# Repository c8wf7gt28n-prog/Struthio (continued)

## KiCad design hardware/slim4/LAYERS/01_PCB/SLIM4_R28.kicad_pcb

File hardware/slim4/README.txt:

STRUTHIO SLIM4 — R32 PACKAGE

R32 puts PCB R27 in the package: PCB R26 with the margins found by a five-part pre-order review
(CHECKS/PREORDER_REVIEW_R26/: power, processor, display, audio and controls, firmware; no blocker in
the hardware). 31 ground vias in U1's exposed pad (R26: 4), each on the pad's copper; 10 uF at
U1's core supply pins; a second 1 uF on the backlight output and a 60 V backlight diode; R424
beside the charger (BQ_TS 5.2 mm, was 88 mm); 22 ohm on the USB data lines; silkscreen labels at
the battery, speaker and button positions. The ground under the core regulator's feedback and
enable routes is checked unbroken (LAYERS/01_PCB/R27_FROM_R26/PLANE_CHECK_R27.txt). The DSI pairs,
pins, ports and outline are unchanged. Four parts plug into it with no soldering and no adapter
cables: the Crystalfontz 5 in panel (its own tail into J1), a protected 1-cell battery of 1000 mAh
or more (JST PH, reverse-polarity switch), and two speakers (Molex PicoBlade). The firmware for it
is firmware/slim4 in the repository (R12: a hardware self-test at every boot and a USB console for
bring-up, docs/FIRST_BOOT.md). LAYERS/01_PCB/BRINGUP_PROCEDURE.md is the probe procedure for the
first boards. What R32 decided and why is in DECISIONS_R32.md (R31's to R26's decisions still hold
where not replaced). The case was set aside by the owner.

  01_PCB          R27: the four plug-in ports, a top-contact display socket on the front under the
                  panel, DSI coupled pairs from U1 to J1 over ground with return vias, power planes and
                  datasheet layouts for the 3.3 V, 1.2 V and backlight converters, 31 ground vias in
                  U1's exposed pad, 74 mA backlight, 0.5 A charging. JLCPCB order
                  files are generated by CHECKS/build_builder_packs.py. KiCad DRC 0/0/0.
                  One part to source: U1 (ESP32-P4NRW32X) had no stock on 2026-10-07.
  02_CASE         R12: complete enclosure, converged on R21 for a HOTHMI-size panel. Set aside:
                  its pass for the 5 in panel and the R23-R27 connectors is open.
  03_ACRYLIC      R2: clear unprinted face film (on hold with the case).

CHECKS/convergence_check.py tests every interface between the layers:
  - board against the walls, LCD against the shell, caps against the switches, film against the relief;
  - parts against parts, at rest and pressed;
  - supports against pads, joints, speakers, USB-C and battery;
  - J1's 40 pads against the panel's published pin table (N1).
Result: 78 PASS · 3 FAIL · 9 GATE · 3 INFO (CHECKS/R32_CONVERGENCE_REPORT.md).
The 3 FAIL rows are the set-aside case: the 5 in panel does not fit the R12 pocket (C6), and the
rear shell meets the new J3/J5 bodies and sits 0.08 mm from J4 (F1, G1). PRODUCTION_GATES.md lists
what is open, in the order to do it.

Shared CAD datum: millimetres, SLIM4 PCB XY (R21 = R22 = R23 = R24 = R25 = R26 = R27; Y down), board bottom at Z=0, +Z
toward the front.

Start with:
  index.html                          the studio: PCB, CASE and ACRYLIC layers; copper pours,
                                      BOM and sourcing for each part, fab status, open items; a guided tour;
                                      SYSTEMS (the board by function), BENCH (a bring-up record per board,
                                      step by step, exported as JSON/CSV) and DOCS (these documents, offline)
  PRODUCTION_GATES.md                 what to order now, then, and in the case pass
  LAYERS/01_PCB/README_PCB_LAYER.md   R27, R26, R25, R24 and R23 changes, battery, sourcing U1, rebuild
  LAYERS/01_PCB/BRINGUP_PROCEDURE.md  probing the first boards, phase by phase
  CHECKS/PREORDER_REVIEW_R26/         the five pre-order reviews
  CHECKS/R27_DSI_REPORT.md            the DSI pairs measured on the board
  LAYERS/01_PCB/DISPLAY_PORT.md       the panel, the J1 pinout and how the tail folds in
  LAYERS/01_PCB/FIRMWARE_PINMAP.md    every ESP32-P4 GPIO, for the firmware
  LAYERS/01_PCB/RELEASE_GATES.md      what is closed and open on the board
  CHECKS/R32_CONVERGENCE_REPORT.md    what was checked
  AI_CHANGE_REPORT_R32.md, CHANGELOG.md

Package layout:
  LAYERS/01_PCB          R27 KiCad board, project, footprints, layer JSON, DRC, reviews,
                         bring-up procedure, R27_FROM_R26/, R26_FROM_R25/, R25_FROM_R24/, R24_FROM_R23/, R23_FROM_R22/ and R22_FROM_R21/ (the scripted edits)
  LAYERS/02_CASE         CASE R12 source (build_r12.py, export_layer_formats.py) and exports;
                         the same source also builds the ACRYLIC film
  LAYERS/03_ACRYLIC      film R2 outputs
  ASSEMBLY/              PCB, case and film in one STEP, and the build order
  CHECKS/                convergence checker and reports, PCB layer exporter, renderer and renders,
                         component heights, BOM sourcing, fab summary, DSI pair check, pre-order reviews, manifest,
                         viewer-bundle and builder-file generators
  REFERENCES/            reference only: PCB R26, R25, R24, R23, R22 and R21, the R22 display flex, the R10 fit study,
                         the SLIM4 R3 study, the CASE R13 symmetric-controls prototype and the R1 outline study
  root                   studio (index.html, app.js, eye.js, styles.css, eye.css, model-data.js,
                         case-layer-data.js, acrylic-layer-data.js, case-r3-data.js, case-r13-data.js,
                         bench.js, bench.css, bench-data.js,
                         R27_REAR_BOARD.svg, sw.js, manifest, icons), package docs,
                         requirements.txt, PROJECT_MANIFEST.json, SHA256SUMS.txt

Regenerate everything (Python 3.13 with requirements.txt; KiCad 7.0.x for the PCB steps, with its
pcbnew module importable from that Python). Run from
the package root, in this order:
  python3 CHECKS/export_pcb_layer.py LAYERS/01_PCB/SLIM4_R27.kicad_pcb REFERENCES/PCB_R21/SLIM4_R21_PCB_LAYER.json \
      LAYERS/01_PCB/SLIM4_R27_PCB_LAYER.json R27 "STRUTHIO SLIM4 PCB R27" "Order files ready · U1 stock to confirm"
                                         (only after a PCB edit; then update the A1 hashes)
  python3 CHECKS/dsi_pair_check.py LAYERS/01_PCB/SLIM4_R27.kicad_pcb CHECKS/R27_DSI_REPORT   (after a PCB edit)
  python -B LAYERS/02_CASE/export_layer_formats.py
  python -B CHECKS/build_builder_packs.py <folder outside the package>
                                         (writes CHECKS/R27_FAB_SUMMARY.json)
  python -B CHECKS/convergence_check.py
  python -B CHECKS/build_builder_packs.py <folder outside the package>   (again: its README quotes the report)
  python -B CHECKS/render_review.py
  python -B CHECKS/build_pcb_viewer_data.py      (also the SYSTEMS map: every part and net assigned, or it stops)
  python -B CHECKS/build_bench_data.py           (bring-up steps and documents for BENCH and DOCS)
  python -B CHECKS/build_r13_reference_data.py   (the R13 controls prototype layer)
  python -B CHECKS/make_manifest.py      (last)

Files for the builders:
  python -B CHECKS/build_builder_packs.py <folder outside the package>
writes STRUTHIO_SLIM4_R32_BUILDER_FILES/ and its zip:
  1_PCB_FABRICATION  JLCPCB order: Gerbers, drill, BOM, CPL, README with every option and the
                     four plug-in parts
  2_3D_PRINTING      case R12 parts. On hold: do not print before the case pass.
  3_ACRYLIC_STICKER  face film, tapes, cover glass (on hold with the case)
The board is plotted from a temporary copy, with its hash checked before and after.

Deploying the studio: publish a bundle, not this folder.
  python -B CHECKS/build_viewer_bundle.py <folder outside the package>
writes 7 files: index.html, studio.js, R27_REAR_BOARD.svg, sw.js, manifest and two icons.

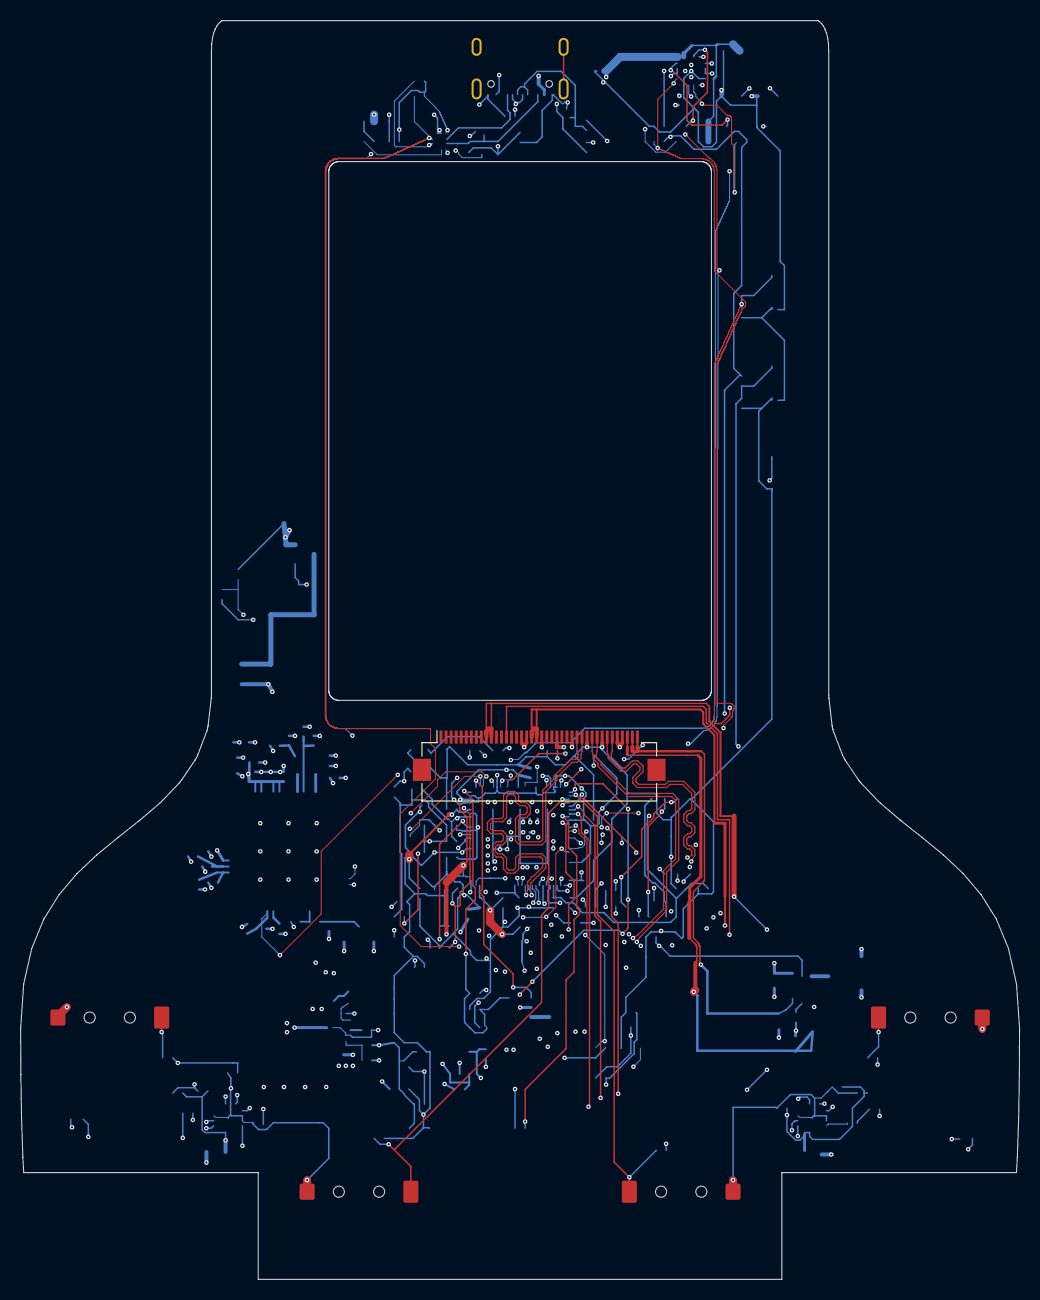
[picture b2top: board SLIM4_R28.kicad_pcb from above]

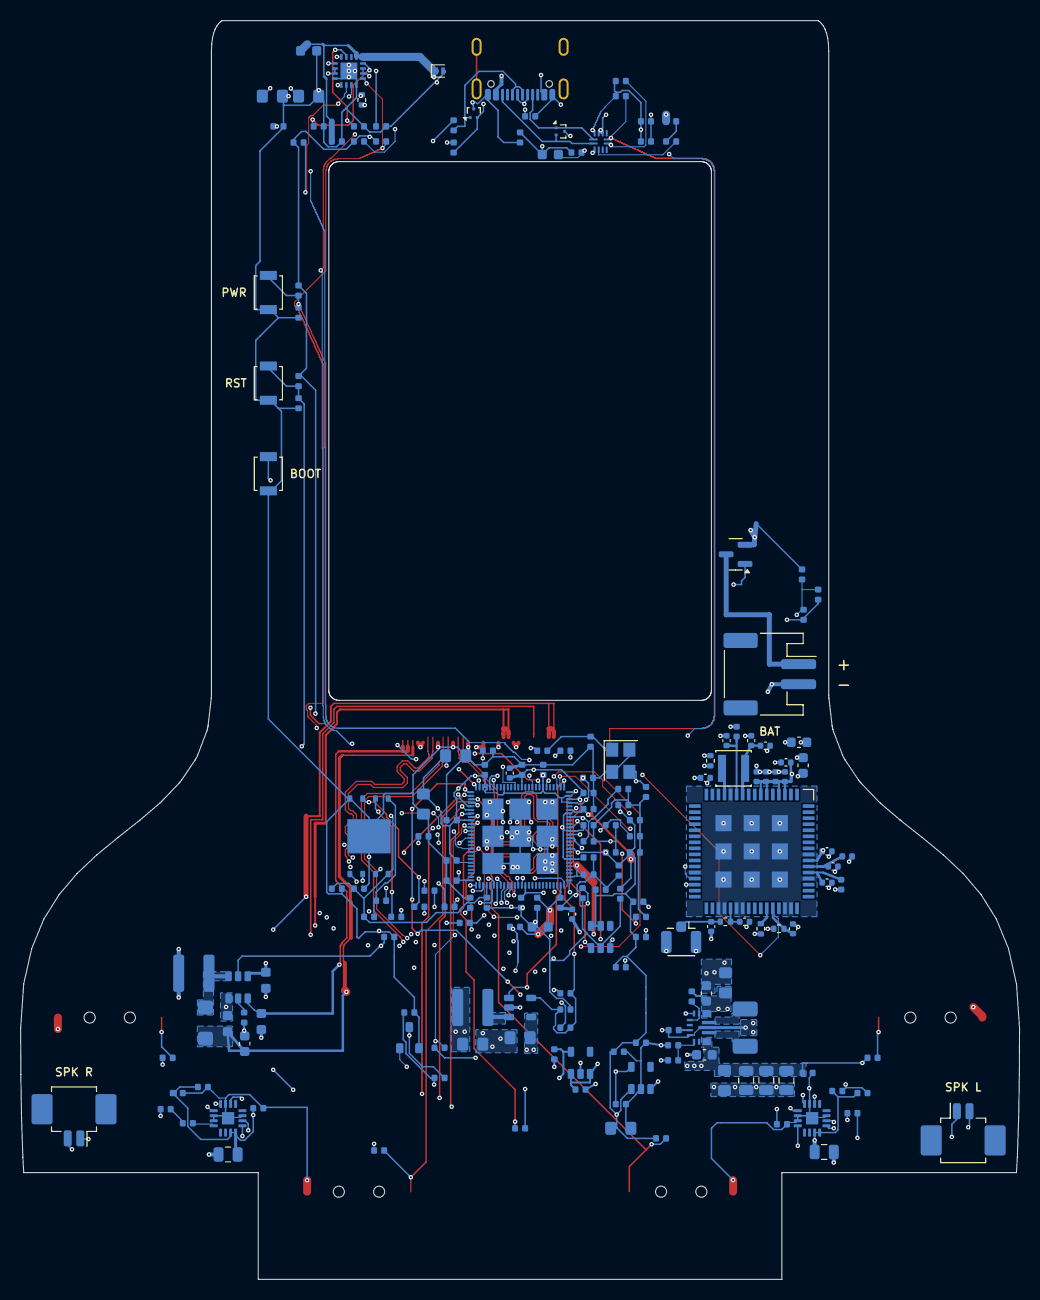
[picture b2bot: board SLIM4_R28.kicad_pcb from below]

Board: 6 copper layers, 99.2 x 125.0 mm, 194 parts (189 on the bottom side), 104 nets.

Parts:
C101: CL05B104KO5NNNC; FP_C101
C102: CL05B104KO5NNNC; FP_C102
C103: CL05B104KO5NNNC; FP_C103
C104: CL05B104KO5NNNC; FP_C104
C105: CL05B104KO5NNNC; FP_C105
C106: CL05B104KO5NNNC; FP_C106
C107: CL05B103KB5NNNC; FP_C107
C108: CL05B104KO5NNNC; FP_C108
C109: CL05A105KA5NQNC; FP_C109
C110: CL05B103KB5NNNC; FP_C110
C111: CL05B104KO5NNNC; FP_C111
C112: CL10A475KO8NNNC; FP_C112
C113: CL05B104KO5NNNC; FP_C113
C114: CL05B104KO5NNNC; FP_C114
C115: CL05A105KA5NQNC; FP_C115
C116: CL05B104KO5NNNC; FP_C116
C117: CL05B104KO5NNNC; FP_C117
C118: CL05A105KA5NQNC; FP_C118
C119: CL05A105KA5NQNC; FP_C119
C120: CL05A105KA5NQNC; FP_C120
C121: CL05A105KA5NQNC; FP_C121
C122: CL05A105KA5NQNC; FP_C122
C123: CL21A106KAYNNNE; FP_C123
C124: CL05B104KO5NNNC; FP_C124
C125: CL05B104KO5NNNC; FP_C125
C126: CL21A106KAYNNNE; FP_C126
C127: CL05B104KO5NNNC; FP_C127
C128: CL05B104KO5NNNC; FP_C128
C129: CL05B104KO5NNNC; FP_C129
C130: CL05B104KO5NNNC; FP_C130
C131: CL05B104KO5NNNC; FP_C131
C132: CL05B104KO5NNNC; FP_C132
C133: CL21A106KAYNNNE; FP_C133
C134: 0402 C0G 22pF; FP_C134
C135: CL21A226MQQNNNE; FP_C135
C136: CL05A105KA5NQNC; FP_C136
C138: CL05A106MQ5NUNC; FP_C138
C139: CL05A106MQ5NUNC; FP_C139
C140: CL10A105KB8NNNC; FP_C140
C201: CL05B104KO5NNNC; FP_C201
C202: CL05A105KA5NQNC; FP_C202
C203: 0402CG120J500NT; FP_C203
C204: 0402CG120J500NT; FP_C204
C302: CL05B104KO5NNNC; FP_C302
C303: CL05B104KO5NNNC; FP_C303
C304: CL05B104KO5NNNC; FP_C304
C305: CL05A105KA5NQNC; FP_C305
C306: CL05A105KA5NQNC; FP_C306
C307: CL05A105KA5NQNC; FP_C307
C308: CL05A105KA5NQNC; FP_C308
C309: CL10A105KB8NNNC; FP_C309
C310: CL05B224KO5NNNC; FP_C310
C311: CL10A475KO8NNNC; FP_C311
C401: CL05B104KO5NNNC; FP_C401
C402: CL10A106KP8NNNC; FP_C402
C403: CL05B104KO5NNNC; FP_C403
C404: CL05B104KO5NNNC; FP_C404
C406: CL05B104KO5NNNC; FP_C406
C407: CL05B104KO5NNNC; FP_C407
C408: CL05A105KA5NQNC; FP_C408
C409: CL10A475KO8NNNC; FP_C409
C410: CL10A475KO8NNNC; FP_C410
C411: CL21A106KAYNNNE; FP_C411
C412: CL21A106KAYNNNE; FP_C412
C413: CL21A226MQQNNNE; FP_C413
C414: CL21A226MQQNNNE; FP_C414
C415: CL21A226MQQNNNE; FP_C415
C416: CL10A106KP8NNNC; FP_C416
C417: CL21A226MQQNNNE; FP_C417
C418: CL21A226MQQNNNE; FP_C418
C419: CL21A226MQQNNNE; FP_C419
C420: CL21A106KAYNNNE; FP_C420
C421: CL21A106KAYNNNE; FP_C421
C501: CL05B104KO5NNNC; FP_C501
C502: CL05B104KO5NNNC; FP_C502
C503: CL05B104KO5NNNC; FP_C503
C504: CL05B104KO5NNNC; FP_C504
C505: CL05A105KA5NQNC; FP_C505
C506: CL05A105KA5NQNC; FP_C506
C601: CL05B104KO5NNNC; FP_C601
C602: CL05B104KO5NNNC; FP_C602
C603: CL05B104KO5NNNC; FP_C603
C701: CL05A106MQ5NUNC; FP_C701
C711: CL05B104KO5NNNC; FP_C711
C712: CL05A105KA5NQNC; FP_C712
C713: CL05B104KO5NNNC; FP_C713
C714: CL05B104KO5NNNC; FP_C714
C715: CL05A105KA5NQNC; FP_C715
C716: CL10A475KO8NNNC; FP_C716
C717: CL10A475KO8NNNC; FP_C717
C718: CL05A474KA5NNNC; FP_C718
C719: CL05B104KO5NNNC; FP_C719
C720: CL05B104KO5NNNC; FP_C720
C721: CL05B104KO5NNNC; FP_C721
C722: CL05A105KA5NQNC; FP_C722
C723: CL05A105KA5NQNC; FP_C723
C724: DNP; FP_C724
C725: DNP; FP_C725
C726: CL05B104KO5NNNC; FP_C726
D1: PESD5V0S1UL,315; FP_D1
D2: STPS1L60ZFY; FP_D2
E701: BLM15AG121SN1D; FP_E701
E702: BLM15AG121SN1D; FP_E702
E703: BLM15AG121SN1D; FP_E703
J1: FH12A-40S-0.5SH(55); FP_J1
J2: USB4105-GF-A-120; FP_J2
J3: S2B-PH-SM4-TB(LF)(SN); FP_J3
J4: 53261-0271; FP_J4
J5: 53261-0271; FP_J5
J701: U.FL-R-SMT-1(10); FP_J701
L1: MWSA0402S-1R0MT; FP_L1
L2: ASWPA4035S2R2MT; FP_L2
L3: WPN4020H100MT; FP_L3
L701: SWPA3012S150MT; FP_L701
Q1: 2N7002; FP_Q1
Q2: AO3401A; FP_Q2
R103: 0402WGF4021TCE; FP_R103
R104: 0402WGF4993TCE; FP_R104
R105: 0402WGF4993TCE; FP_R105
R106: 0402WGF1002TCE; FP_R106
R107: 0402WGF1002TCE; FP_R107
R108: 0402WGF1002TCE; FP_R108
R109: 0402WGF1002TCE; FP_R109
R110: 0402WGF1002TCE; FP_R110
R111: 0402WGF1002TCE; FP_R111
R112: 0402WGF1002TCE; FP_R112
R201: 0402WGF0000TCE; FP_R201
R202: 0402WGF0000TCE; FP_R202
R203: 0402WGF0000TCE; FP_R203
R204: 0402WGF0000TCE; FP_R204
R205: 0402WGF0000TCE; FP_R205
R206: 0402WGF0000TCE; FP_R206
R207: 0402WGF0000TCE; FP_R207
R208: 0402WGF0000TCE; FP_R208
R209: 0402WGF1002TCE; FP_R209
R307: 0402WGF1002TCE; FP_R307
R308: 0402WGF1003TCE; FP_R308
R309: 0603WAF270KT5E; FP_R309
R401: 0402WGF220JTCE; FP_R401
R402: 0402WGF220JTCE; FP_R402
R403: 0402WGF0000TCE; FP_R403
R404: 0402WGF0000TCE; FP_R404
R410: 0402WGF4703TCE; FP_R410
R411: 0402WGF1503TCE; FP_R411
R412: 0402WGF1801TCE; FP_R412
R413: 0402WGF3301TCE; FP_R413
R415: 0402WGF1501TCE; FP_R415
R416: 0402WGF4703TCE; FP_R416
R417: 0402WGF4303TCE; FP_R417
R418: 0402WGF1003TCE; FP_R418
R419: 0402WGF3302TCE; FP_R419
R420: 0402WGF1003TCE; FP_R420
R421: 0402WGF1003TCE; FP_R421
R422: 0402WGF1003TCE; FP_R422
R423: 0402WGF1003TCE; FP_R423
R424: 0402WGF1002TCE; FP_R424
R501: 0402WGF2001TCE; FP_R501
R502: 0402WGF1003TCE; FP_R502
R503: 0402WGF1103TCE; FP_R503
R504: 0402WGF1003TCE; FP_R504
R601: 0402WGF1002TCE; FP_R601
R602: 0402WGF1002TCE; FP_R602
R603: 0402WGF1002TCE; FP_R603
R604: 0402WGF1002TCE; FP_R604
R605: 0402WGF1002TCE; FP_R605
R606: 0402WGF1002TCE; FP_R606
R607: 0402WGF1002TCE; FP_R607
R701: 0402WGF0000TCE; FP_R701
R702: 0402WGF1002TCE; FP_R702
R703: 0402WGF1002TCE; FP_R703
R704: 0402WGF0000TCE; FP_R704
SW1: D2LS-21; FP_SW1
SW2: D2LS-21; FP_SW2
SW3: D2LS-21; FP_SW3
SW4: D2LS-21; FP_SW4
SW5: B3U-1000P; FP_SW5
SW6: B3U-1000P; FP_SW6
SW7: B3U-1000P; FP_SW7
U1: ESP32-P4NRW32X; FP_U1
U2: W25Q512JVEIQ TR; FP_U2
U3: TLV62569DBVR; FP_U3
U4: TPS63070RNMR; FP_U4
U5: TLV75518PDBVR; FP_U5
U6: ME6211C30M5G-N; FP_U6
U7: TPS61165DBVR; FP_U7
U8: MAX98357AETE+T; FP_U8
U9: MAX98357AETE+T; FP_U9
U10: BQ24074RGTR; FP_U10
U11: TPD2EUSB30DRTR; FP_U11
U12: TPD2EUSB30DRTR; FP_U12
U13: TUSB320LAIRWBR; FP_U13
U14: TPS3808G33DBVR; FP_U14
U15: RAK3172-SIP-9-SM-NI; FP_U15
Y1: L327S400H11L; FP_Y1

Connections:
1V1_HP: C103.1, C105.1, C125.1, C129.1, C134.1, C135.1, C138.1, C139.1, L2.2, R104.1, U1.26, U1.54, U1.76, U1.91
3V3_ENABLE: R423.2, U4.1, U4.14
3V3_SYS: C101.1, C102.1, C106.1, C114.1, C117.1, C123.1, C124.1, C126.1, C127.1, C128.1, C130.1, C131.1, C132.1, C133.1, C302.1, C303.1, C305.1, C307.1, C404.1, C406.1, C407.1, C408.1, C410.1, C414.1, C415.1, C416.1, C417.1, C418.1, C419.1, R106.1, R108.1, R109.1, R110.1, R111.1, R112.1, R308.1, R403.1, R410.1, R420.1, R421.1, R601.1, R602.1, R603.1, R605.1, R606.1, R607.1, R701.1, U1.9, U1.21, U1.62, U1.75, U1.77, U1.85, U1.96, U1.101, U1.102, U3.4, U4.7, U4.8, U5.1, U5.3, U6.1, U6.3, U13.12, U14.5, U14.6
AUDIO_SD_CTRL: R501.1, R502.1, R504.1, U1.8
AUDIO_SD_L: R501.2, U8.4
AUDIO_SD_R: R503.2, U9.4
AUDIO_SD_R_MID: R502.2, R503.1
BACKLIGHT_PWM: R422.1, U1.10, U7.2
BAT_ADC: C603.1, R418.2, R419.1, U1.17
BAT_CONN: J3.1, Q2.3
BAT_PLUS: C412.1, Q2.2, R418.1, U10.2, U10.3
BL_COMP: C310.1, U7.5
BL_SW: D2.A, L3.2, U7.3
BOOT_STRAP: R108.2, SW7.1, U1.66
BQ_EN1: R603.2, U1.14, U10.6
BQ_EN2: R604.1, U1.88, U10.5
BQ_ILIM: R415.1, U10.12
BQ_ISET: R412.1, U10.16
BQ_ITERM: R413.1, U10.15
BQ_TS: R424.1, U10.1
BTN_LEFT: R111.2, SW1.COM, U1.1
BTN_RIGHT: R112.2, SW2.COM, U1.2
CHASSIS_GND: J2.SH, R404.1
CHG_STATUS: R420.2, U1.12, U10.9
CHIP_PU: C136.1, R106.2, U1.103, U14.1
CORE_SW: L2.1, U3.3
DART_LEFT: R601.2, SW3.COM, U1.3
DART_RIGHT: R602.2, SW4.COM, U1.4
DOWNLOAD_STRAP_GPIO36: R109.2, U1.68
DSI_REXT: R103.1, U1.34
EN_DCDC: U1.79, U3.1
FB_DCDC: C134.2, R104.2, R105.1, U1.78, U3.5
FLASH_CLK: R202.2, U2.6
FLASH_CLK_SOC: R202.1, U1.32
FLASH_CS_N: R201.2, R209.2, U2.1
FLASH_CS_SOC: R201.1, U1.27
FLASH_IO0: R203.2, U2.5
FLASH_IO0_SOC: R203.1, U1.33
FLASH_IO1: R204.2, U2.2
FLASH_IO1_SOC: R204.1, U1.28
FLASH_IO2: R205.2, U2.3
FLASH_IO2_SOC: R205.1, U1.29
FLASH_IO3: R206.2, U2.7
FLASH_IO3_SOC: R206.1, U1.31
GND: C101.2, C102.2, C103.2, C104.2, C105.2, C106.2, C107.2, C108.2, C109.2, C110.2, C111.2, C112.2, C113.2, C114.2, C115.2, C116.2, C117.2, C118.2, C119.2, C120.2, C121.2, C122.2, C123.2, C124.2, C125.2, C126.2, C127.2, C128.2, C129.2, C130.2, C131.2, C132.2, C133.2, C135.2, C136.2, C138.2, C139.2, C140.2, C201.2, C202.2, C203.2, C204.2, C302.2, C303.2, C304.2, C305.2, C306.2, C307.2, C308.2, C309.2, C310.2, C311.2, C401.2, C402.2, C403.2, C404.2, C406.2, C407.2, C408.2, C409.2, C410.2, C411.2, C412.2, C413.2, C414.2, C415.2, C416.2, C417.2, C418.2, C419.2, C420.2, C421.2, C501.2, C502.2, C503.2, C504.2, C505.2, C506.2, C601.2, C602.2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
I2S_BCLK: U1.5, U8.16, U9.16
I2S_DOUT: U1.7, U8.1, U9.1
I2S_LRCLK: U1.6, U8.14, U9.14
LCD_1V8: C304.1, C306.1, J1.19, J1.20, R307.1, U5.5
LCD_LED_A: C140.1, C309.1, D2.K, J1.38
LCD_LED_K: J1.39, J1.40, R309.1, U7.6
LCD_RESET_GATE: Q1.1, R308.2, U1.11
LCD_RESX: J1.14, Q1.3, R307.2
LCD_VCI_3V0: C308.1, J1.10, J1.11, U6.5
MIPI_DSI_CLK_N: J1.29, U1.37
MIPI_DSI_CLK_P: J1.28, U1.38
MIPI_DSI_D0_N: J1.35, U1.40
MIPI_DSI_D0_P: J1.34, U1.39
MIPI_DSI_D1_N: J1.32, U1.36
MIPI_DSI_D1_P: J1.31, U1.35
PGOOD_STATUS: R421.2, U1.86, U10.7
PWR_WAKE: C601.1, R110.2, SW5.1, U1.104
RADIO_3V3: C701.1, C711.1, C712.1, C713.1, C714.1, C715.1, C716.1, C717.1, C721.2, E701.2, E702.1, E703.1, R701.2, R703.2, U15.3, U15.4, U15.6, U15.7, U15.55
RADIO_ANT: C725.2, J701.1, R704.2
RADIO_BOOT0: R702.2, U15.43
RADIO_NRST: C726.1, R703.1, U1.93, U15.44
RADIO_RF: C724.2, R704.1, U15.37
RADIO_UART_RX: U1.81, U15.29
RADIO_UART_TX: U1.80, U15.30
RADIO_VDDPA: C723.2, E703.2, U15.53
RADIO_VDDRF: C722.2, E702.2, U15.54
RADIO_VDDSMPS: C720.1, E701.1, U15.11
RADIO_VFB: C718.1, C719.2, L701.1, U15.10
RADIO_VLX: L701.2, U15.13
RESET_MR: C602.1, R607.2, SW6.1, U14.3
SPK_L_N: J4.2, U8.10
SPK_L_P: J4.1, U8.9
SPK_R_N: J5.2, U9.10
SPK_R_P: J5.1, U9.9
STRAP_GPIO34: R107.1, U1.65
SYS_RAW: C311.1, C402.1, C411.1, C413.1, C420.1, C421.1, C501.1, C502.1, C503.1, C504.1, C505.1, C506.1, L3.1, R423.1, U4.12, U4.13, U7.1, U8.7, U8.8, U9.7, U9.8, U10.10, U10.11
U4_FB: R410.2, R411.1, U4.5
U4_L1_SW: L1.1, U4.11
U4_L2_SW: L1.2, U4.9
U4_VAUX: C401.1, U4.3
USB_CC1: J2.A5, U12.1, U13.1
USB_CC2: J2.B5, U12.2, U13.2
USB_CURR_OUT1: R605.2, U1.84, U13.7
USB_CURR_OUT2: R606.2, U1.18, U13.8
USB_DM_CONN: J2.A7, J2.B7, R402.2, U11.2
USB_DP_CONN: J2.A6, J2.B6, R401.2, U11.1
USB_JTAG_DM: R402.1, U1.52
USB_JTAG_DP: R401.1, U1.53
USB_VBUS: C403.1, C409.1, D1.1, J2.A4, J2.A9, J2.B4, J2.B9, R416.1, U10.13
USB_VBUS_SENSE: R417.2, U13.4
USB_VBUS_SENSE_MID: R416.2, R417.1
VDDO_FLASH_3V3: C104.1, C115.1, C120.1, C201.1, C202.1, R209.1, U1.30, U1.71, U2.8
VDDO_MIPI_2V5: C107.1, C108.1, C109.1, C122.1, U1.41, U1.73
VDDO_PSRAM_1V9: C113.1, C116.1, C118.1, C119.1, C121.1, U1.59, U1.67, U1.72
VDD_USBPHY_LOCAL: C110.1, C111.1, C112.1, R403.2, U1.51
XTAL_N: C204.1, R208.2, Y1.3
XTAL_N_SOC: R208.1, U1.99
XTAL_P: C203.1, R207.2, Y1.1
XTAL_P_SOC: R207.1, U1.100

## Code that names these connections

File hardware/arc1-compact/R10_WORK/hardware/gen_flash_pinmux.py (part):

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
# ---------------- 1. F133 system NOR (sole bus master, memory spec s3.1) ----------------
NOR_PART = "W25Q512JVFIQ (64 MiB, SOIC16 300 mil)"
NOR = [("SPI0_CLK", "PC2", "SPI0-CLK", "out", "16 CLK"), ("SPI0_CS0_N", "PC3", "SPI0-CS0", "out", "7 /CS"),
       ("SPI0_MOSI", "PC4", "SPI0-MOSI", "out", "15 DI/IO0"), ("SPI0_MISO", "PC5", "SPI0-MISO", "in", "8 DO/IO1"),
       ("SPI0_IO2", "PC6", "SPI0-WP", "io", "9 /WP/IO2"), ("SPI0_IO3", "PC7", "SPI0-HOLD", "io", "1 /HOLD/IO3")]
for sig, pad, fn, d, np in NOR:
    f133("NOR", sig, pad, fn, d, NOR_PART, np, "SELECTED; boot validation pending",
         "Winbond Rev.B Figure 1b; Q suffix QE defaults to 1; dedicated RESET pin 3")
for pin, fn, net in [(2, "VCC", "3V3"), (3, "/RESET", "NOR_RESET_N"), (10, "GND", "GND")] + [(p, "NC", "NO_CONNECT") for p in [4, 5, 6, 11, 12, 13, 14]]:
    add("NOR_AUX", fn, NOR_PART, str(pin), fn, "NOR", "3.3 V" if fn in ("VCC", "/RESET") else ("0 V" if fn == "GND" else "-"),
        "in" if fn == "/RESET" else ("nc" if fn == "NC" else "power"), net, "-", "SELECTED; schematic pending",
        "Independent hardware reset; do not use IO3 as reset" if fn == "/RESET" else "Winbond Rev.B Figure 1b")

# ---------------- 2. F133 -> 12F slave SPI configuration (shares SPI0 behind isolation buffers, as R8.5-C) -------------
CFG12 = [("FPGA12_SCK", "PC2", "SPI0-CLK", "out", 54, "CCLK", "via isolation buffer (R8.5-C U21)"),
         ("FPGA12_MOSI", "PC4", "SPI0-MOSI", "out", 47, "PB11B", "D0/MOSI, via buffer (U22)"),
         ("FPGA12_MISO", "PC5", "SPI0-MISO", "in", 46, "PB11A", "D1/MISO, via buffer (U24, enabled by SN low)"),
         ("FPGA12_SS_N", "PE4", "GPIO-OUT", "out", 48, "PB13A", "SN/CSN, software chip select")]
for sig, pad, fn, d, tq, pf, note in CFG12:
    p12("CFG12", sig, tq, pf, "in" if d == "out" else "out", "F133-B", pad, "SELECTED (R8.5-C loader, now for the 12F)",
        note, config=(pf == "CCLK"))
for sig, pad, fn, d, tq, pf in [("FPGA12_PROGRAMN", "PE8", "GPIO open-drain", "od", 57, "PROGRAMN"),
                                ("FPGA12_INITN", "PD0", "GPIO-IN", "in", 55, "INITN"),
                                ("FPGA12_DONE", "PE9", "PE-EINT9", "in", 56, "DONE")]:
    p12("CFG12", sig, tq, pf, "bidir" if pf != "PROGRAMN" else "in", "F133-B", pad, "SELECTED", "dedicated sysCONFIG pin", config=True)
for sig, tq, pf, lvl in [("FPGA12_CFG0", 62, "CFG_0", "pull-up 10k"), ("FPGA12_CFG1", 59, "CFG_1", "GND"), ("FPGA12_CFG2", 58, "CFG_2", "GND")]:
    p12("CFG12", sig, tq, pf, "in", "strap", lvl, "SELECTED", "CFG[2:0] = 001 slave SPI (TN-02039)", config=True)
for sig, pad, fn, d in [("FPGA12_BUS_EN_N", "PE6", "GPIO-OUT", "out"), ("FPGA12_PWR_EN", "PE0", "GPIO-OUT", "out"),
                        ("FPGA12_VCC_PG", "PD1", "GPIO-IN", "in")]:
    f133("CFG12", sig, pad, fn, d, "12F power / isolation", "-", "SELECTED (R8.5-C function, retargeted to the 12F)")

# ---------------- 3. 12F 4 MiB QSPI PSRAM (memory spec s2.4) on bank 3 ----------------
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            lst.append(("# " if lst is lpf12_tq else "") + f'IOBUF PORT "{port}" IO_TYPE=LVCMOS33 {io} ;')

# ---------------- 4. D213 -> 45F slave SPI configuration (memory spec s3.1) ----------------
CFG45 = [("FPGA45_SCK", "PB11", "SPI1_CLK", "out", "U3", "CCLK"), ("FPGA45_MOSI", "PB10", "SPI1_MOSI", "out", "W2", "D0/MOSI"),
         ("FPGA45_MISO", "PB9", "SPI1_MISO", "in", "V2", "D1/MISO"), ("FPGA45_SS_N", "PB8", "SPI1_CS", "out", "T2", "SN/CSN")]
for sig, pad, fn, d, ball, what in CFG45:
    d213("CFG45", sig, pad, fn, d, "LFE5U-45F", ball, "PROPOSED", "D213 SPI1 (VCC33_IO0); PB0-PB5 stay free for a D213 boot NOR")
    p45("CFG45", sig, ball, "in" if d == "out" else "out", "D213ECV", pad, "PROPOSED", what, config=(ball == "U3"))
for sig, pad, ball in [("FPGA45_PROGRAMN", "PA4", "W3"), ("FPGA45_INITN", "PA5", "V3"), ("FPGA45_DONE", "PA6", "Y3")]:
    d213("CFG45", sig, pad, "GPIO", "od" if "PROG" in sig else "in", "LFE5U-45F", ball, "PROPOSED",
         "GPIO; PA0/PA1 (UART0) and PA8-PA11 (JTAG alternate) avoided")
    p45("CFG45", sig, ball, "in" if "PROG" in sig else "bidir", "D213ECV", pad, "PROPOSED", "dedicated sysCONFIG pin", config=True)
p45("CFG45", "FPGA45_CFG0", "U4", "in", "strap", "pull-up 10k", "SELECTED (R8.5-C)", "CFG[2:0] = 001 slave SPI", config=True)

# ---------------- 5. D213 boot NOR fallback (memory spec s7.2) and USB link ----------------
for sig, pad, fn in [("D213_NOR_HOLD", "PB0", "SPI0_HOLD"), ("D213_NOR_WP", "PB1", "SPI0_WP"), ("D213_NOR_CS", "PB2", "SPI0_CS"),
                     ("D213_NOR_MISO", "PB3", "SPI0_MISO"), ("D213_NOR_MOSI", "PB4", "SPI0_MOSI"), ("D213_NOR_CLK", "PB5", "SPI0_CLK")]:
    d213("D213NOR", sig, pad, fn, "io", "D213 boot NOR (DNP footprint)", "-", "RESERVED (fallback if flashless boot fails)",
         allow_matrix=True)

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
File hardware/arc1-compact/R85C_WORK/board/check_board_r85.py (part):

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
@rule
def boot_straps_00(c):
    """BOOT-SEL[1:0] = 00 (SPI NOR first): PC4 and PC5 each have one populated pull-down <= 3.6k to GND and no pull-up"""
    errs = []
    for pname in ("PC4", "PC5"):
        net = c.f133(pname)
        rs = [r for r in c.resistors(net) if not r[3]]
        pd = [r for r in rs if r[1] == "GND"]
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
@rule
def spi0_fpga_isolated(c):
    """no FPGA (U18) ball on any F133 SPI0 net; every other driver on PC4/PC5 is the NOR or a 3-state buffer
    whose OE# is pulled up (disabled at reset)"""
    errs = []
    for pname in ("PC2", "PC3", "PC4", "PC5", "PC6", "PC7"):
        net = c.f133(pname)
        for ref, pin in c.on_net(net):
            part = c.part(ref)
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    if len(nors) != 1:
        return [f"expected one W25Q256JVFIQ, found {len(nors)}"]
    n = nors[0]["ref"]
    want = {"7": c.f133("PC3"), "16": None, "15": c.f133("PC4"), "8": c.f133("PC5"), "9": c.f133("PC6"), "1": c.f133("PC7")}
    for pin, net in want.items():
        if net and c.net_of(n, pin) != net:
            errs.append(f"NOR pin {pin} on {c.net_of(n, pin)}, expected {net}")
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
@rule
def mn820_miso_buffered(c):
    """F133 PD13 (BT_MISO) is driven by a 3-state buffer from the module, never by the module connector directly"""
    errs = []
    net = c.f133("PD13")
    refs = [(r, p) for r, p in c.on_net(net)]
    if any(c.part(r) == "MN820_RCPT" for r, _ in refs):
        errs.append(f"module pin directly on F133 MISO net {net}")
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    if len(bufs) != 1:
        errs.append(f"expected one LVC1G125 driving {net}, found {bufs}")
    else:
        if c.net_of(bufs[0], "1") != c.f133("PD10"):
            errs.append("MISO buffer OE# must be BT_SS_N (drive only while selected)")
    return errs

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        errs.append(f"load-switch ON ({on}) is not an AND gate output")
    else:
        ins = {c.net_of(gate[0], "1"), c.net_of(gate[0], "2")}
        if ins != {c.f133("PE7"), "DONE_DLY"}:
            errs.append(f"AND inputs {ins}: expected F133 PSRAM_PWR_REQ and DONE_DLY")
        dly = [r for r, p in c.on_net("DONE_DLY") if c.part(r) == "LVC1G17" and p == "4"]
        if not dly or c.net_of(dly[0], "2") != "DONE_RC" or not any(r[1] == "DONE_RC" for r in c.resistors("FPGA_DONE")):
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        errs.append(f"VCCAUX LDO IN/EN = {aux[2]}/{aux[1]}: must ramp with 3V3_FPGA")
    if not any(r[1] == "GND" and not r[3] for r in c.resistors(en)):
        errs.append(f"{en} lacks a pull-down (FPGA must stay off while F133 is in reset)")
    pe0 = c.f133("PE0")
    if pe0 != en and not any(r[1] == en and ohms(r[2]) >= 470 for r in c.resistors(pe0)):
        errs.append("F133 PE0 does not control the FPGA enable through a series resistor")
    if not any(c.part(r) == "HDR_1x3" for r, _ in c.on_net(en)):
        errs.append("no service jumper to power the FPGA without F133 firmware (JTAG recovery)")
    pg = c.net_of(src["1V1_FPGA"][0], "5")
    if c.f133("PD1") != pg:
        errs.append("VCC power-good is not readable by the F133 (PD1)")
    return errs


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

# R8.5-C RGMII job link: F133 EMAC pin -> ECP5 ball, (F133 pin name, ECP5 RTL direction); F133 DS Table 4-3 F4
RGMII_F133_TX = ("PG3", "PG4", "PG5", "PG6", "PG7", "PG12")     # TXCK TXD0..3 TXCTRL: F133 drives
RGMII_F133_RX = ("PG10", "PG1", "PG2", "PG8", "PG9", "PG0")     # RXCK RXD0..3 RXCTRL: ECP5 drives
_ECP5_BANK = None


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
@rule
def rgmii_link(c):
    """R8.5-C RGMII: each of PG0-PG5, PG6-PG10, PG12 reaches exactly one ECP5 bank-0 ball (hot-socket tolerant top bank)
    through exactly one 15-47 ohm series resistor on the DRIVER side (the driver's net carries only the driver and the
    resistor, and the resistor's placement note names the driver); F133 TXCK lands on a PCLK ball; RX/TX CTL nets have a 10k-1M pull-down; no other load on the
    link; no button left on PG0-PG12"""
    errs = []
    u18 = [x["ref"] for x in c.by_part(FPGA)]
    if len(u18) != 1:
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        bank, dual = ecp5_bank(ball)
        if bank != "0":
            errs.append(f"{pname}: ECP5 ball {ball} in bank {bank}, expected bank 0 (hot-socket tolerant)")
        if pname == "PG3" and not (dual or "").startswith("PCLK"):
            errs.append(f"F133 TXCK lands on {ball} ({dual}), not a PCLK clock input")
        drv_net = fnet if f133_tx else enet
        others = [ref for ref, _ in c.on_net(drv_net) if ref not in ("U15", u18, rref)]
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                 if ref not in ("U15", u18, rref) and not c.part(ref).startswith(("TP", "R0"))]
        if extra:
            errs.append(f"{pname}: unexpected load on {far_net}: {extra}")
        if pname in ("PG12", "PG0"):
            pd = [r for r in c.resistors(far_net) if r[1] == "GND" and not r[3] and 1e4 <= (ohms(r[2]) or 0) <= 1e6]
            if not pd:
                errs.append(f"{pname}: CTL net {far_net} has no 10k-1M pull-down (MAC idle while the far side is off)")
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@rule
def ecp5_sysconfig(c):
    """slave SPI: CFG[2:0]=001, 4.7k pull-ups on PROGRAMN/INITN/DONE/SN, CCLK 510R-1k pull-up, TCK pull-down, TMS/TDI/TDO
    pull-ups (all to VCCIO8); PROGRAMN/INITN/DONE reach F133 PE8/PD0/PE9 and PROGRAMN the JTAG header; no config flash"""
    errs = []
    u = c.by_part(FPGA)[0]
    ball = {p["name"].split("/")[0]: (b, p["net"]) for b, p in u["pins"].items()}
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    vccio8 = [p["net"] for b, p in u["pins"].items() if p["name"] == "VCCIO8"]
    if set(vccio8) != {"3V3_FPGA"}:
        errs.append(f"VCCIO8 on {vccio8}")
    for fn, pname, direct in (("INITN", "PD0", True), ("DONE", "PE9", True), ("PROGRAMN", "PE8", False)):
        net = ball[fn][1]
        f = c.f133(pname)
        if direct and f != net:
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
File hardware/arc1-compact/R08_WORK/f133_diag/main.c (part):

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static void gpio_out(uint32_t pin, int v) { gpio_set(pin, v); gpio_func(pin, 1); }
static void gpio_in(uint32_t pin) { gpio_func(pin, 0); }

/* ---------------- UART0 (PE2/PE3 F6) ---------------- */
static void uart_init(void)
{
    gpio_func(PIN_UART0_TX, 6);
    gpio_func(PIN_UART0_RX, 6);
    REG32(CCU_UART_BGR) |= (1u << 0);
    REG32(CCU_UART_BGR) |= (1u << 16);
    REG32(UART0_BASE + UART_LCR) = 0x83u;
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    static const char *const st[] = { "OK", "BLANK", "BAD_MAGIC", "BAD_HDR_CRC", "BAD_LEN", "BAD_CRC", "IO" };
    gpio_out(PIN_T35_BUS_EN_N, 1);          /* T35 isolation buffers OFF while the NOR is used */
    gpio_out(PIN_T35_SS_N_F, 1);
    for (uint32_t p = PIN_SPI0_CLK_F; p <= PIN_SPI0_MISO; p++) gpio_func(p, 2);
    spi_init(SPI0_BASE, CCU_SPI0_CLK, 0);
    memset(&g_nor, 0, sizeof g_nor);
    rc = nor_init(&g_nor, &hal);
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    uint32_t t;
    (void)g_t35hal;
    *psram = R_SKIP;
    gpio_out(PIN_SPI0_CS0_N, 1); gpio_func(PIN_SPI0_CS0_N, 1);   /* NOR CS# held high by GPIO while the T35 is selected */
    gpio_out(PIN_T35_SS_N_F, 1);
    gpio_out(PIN_T35_BUS_EN_N, 0);                              /* isolation buffers ON */
    if (mbx_read(0x0000, id, 8)) return R_FAIL;
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        *psram = (st & (1u << 7)) && !(st & (1u << 8)) ? R_OK : R_FAIL;
    }
    gpio_set(PIN_T35_BUS_EN_N, 1);                              /* back to isolated */
    gpio_func(PIN_SPI0_CS0_N, 2);
    return R_OK;
}

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    kv("   BOOT_SEL_PAD[12:11]  = ", (REG32(SYSCFG_VER) >> 11) & 3u);     /* expect 0 (BOOT-SEL 00) */
    kv("   eFuse boot select    = ", REG32(SID_BOOTSEL));
    kv("   RTC fast boot        = ", REG32(RTC_FASTBOOT));
    gpio_in(PIN_USB_CUR_OUT1); gpio_in(PIN_USB_CUR_OUT2); gpio_in(PIN_VBUS_SENSE);
    kv("S1 USB OUT1/OUT2/VBUS  = ", ((uint32_t)gpio_get(PIN_USB_CUR_OUT1) << 8) | ((uint32_t)gpio_get(PIN_USB_CUR_OUT2) << 4) |
                                     (uint32_t)gpio_get(PIN_VBUS_SENSE));
    r_nor = stage_nor();
    r_bt = stage_bt820();
    r_cfg = stage_t35_config();
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    puts_(" mailbox="); puts_(rs(r_mbx));
    puts_(" psram="); puts_(rs(r_ps));
    puts_("\n(graphics never depends on t35/psram; a lit screen photo is required before any display claim)\n");
    gpio_out(PIN_LED_STATUS, r_bt == R_OK);
    gpio_out(PIN_LED_ERROR, r_nor != R_OK || r_bt != R_OK);
    return 0;
}

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
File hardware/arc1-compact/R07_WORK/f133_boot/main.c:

/* ARC-1 Compact R07 -- F133 bare-metal bring-up image (BUILD-ONLY).
 *
 * Purpose: the first program to run on an ARC-1 board (or a D1s-class dev
 * board wired per R07_WORK/board/r07_board_plan.json). It:
 *   1. prints a banner on UART0 (PE2/PE3, 115200 8N1 from the 24 MHz HOSC),
 *   2. reports boot-select pad status, eFuse boot select and fast-boot register,
 *   3. holds the T35 in reset (PE8 low) -- the FPGA is not needed for graphics,
 *   4. boots the BT820 over SPI1 (PD10..PD13, single mode, ~8 MHz) with the
 *      SAME host-tested driver sources (../firmware/src/bt820_host.c, bt820_gfx.c),
 *   5. reads REG_BOOT_STATUS / REG_CHIP_ID / REG_ID, starts scan-out with the
 *      UNCONFIRMED candidate panel timing and draws a solid test frame,
 *   6. prints every result code so a failure has a signature.
 * Nothing here has executed on silicon. Register addresses come from the
 * D1-H User Manual (see f133_regs.h). Delays use mcycle with an assumed
 * 1.2 GHz worst-case CPU clock, so they are >= the requested time if the
 * clock is slower (likely 24 MHz after BROM: delays then run ~50x long). */
#include <stddef.h>
#include <stdint.h>

#include "bt820_gfx.h"
#include "bt820_regs.h"
#include "f133_regs.h"

/* ---- freestanding libc pieces used by the shared driver ---- */
void *memset(void *d, int c, size_t n) { uint8_t *p = d; while (n--) *p++ = (uint8_t)c; return d; }
void *memcpy(void *d, const void *s, size_t n) { uint8_t *p = d; const uint8_t *q = s; while (n--) *p++ = *q++; return d; }

/* ---- time ---- */
static uint64_t cycles(void) { uint64_t c; __asm__ volatile("csrr %0, mcycle" : "=r"(c)); return c; }
#define ASSUMED_MAX_HZ 1200000000ull
static void delay_us(uint32_t us) {
    uint64_t t0 = cycles(), n = (ASSUMED_MAX_HZ / 1000000ull) * us;
    while (cycles() - t0 < n) { }
}
static uint64_t now_us(void *ctx) { (void)ctx; return cycles() / (ASSUMED_MAX_HZ / 1000000ull); }

/* ---- GPIO ---- */
static void gpio_func(uint32_t port, uint32_t pin, uint32_t fn) {
    uint32_t a = GPIO_CFG(port, pin / 8u), sh = (pin % 8u) * 4u;
    REG32(a) = (REG32(a) & ~(0xFu << sh)) | ((fn & 0xFu) << sh);
}
static void gpio_set(uint32_t port, uint32_t pin, int v) {
    uint32_t a = GPIO_DAT(port);
    REG32(a) = v ? (REG32(a) | (1u << pin)) : (REG32(a) & ~(1u << pin));
}

/* ---- UART0 on PE2/PE3 (Function6, board plan) ---- */
static void uart_init(void) {
    gpio_func(PORT_E, 2, 6);
    gpio_func(PORT_E, 3, 6);
    REG32(CCU_UART_BGR) |= (1u << 0);              /* UART0 gating */
    REG32(CCU_UART_BGR) |= (1u << 16);             /* de-assert UART0 reset */
    REG32(UART0_BASE + UART_LCR) = 0x83u;          /* DLAB, 8N1 */
    REG32(UART0_BASE + UART_DLL) = 13u;            /* 24 MHz / (16 * 13) = 115384 baud (+0.16 %) */
    REG32(UART0_BASE + UART_DLH) = 0u;
    REG32(UART0_BASE + UART_LCR) = 0x03u;
    REG32(UART0_BASE + UART_FCR) = 0x07u;          /* enable + reset FIFOs */
}
static void putc_(char c) {
    while (!(REG32(UART0_BASE + UART_LSR) & (1u << 5))) { }   /* THRE */
    REG32(UART0_BASE + UART_THR) = (uint32_t)(uint8_t)c;
}
static void puts_(const char *s) { while (*s) { if (*s == '\n') putc_('\r'); putc_(*s++); } }
static void puthex(uint32_t v) {
    static const char h[] = "0123456789abcdef";
    puts_("0x");
    for (int i = 7; i >= 0; i--) putc_(h[(v >> (4 * i)) & 0xFu]);
}
static void kv(const char *k, uint32_t v) { puts_(k); puthex(v); puts_("\n"); }

/* ---- SPI1 master, PD10 CS / PD11 CLK / PD12 MOSI / PD13 MISO (Function4) ---- */
#define SPI(o) REG32(SPI1_BASE + (o))
static void spi1_init(void) {
    for (uint32_t p = 10; p <= 13; p++) gpio_func(PORT_D, p, 4);
    REG32(CCU_SPI_BGR) |= (1u << 1);               /* SPI1 gating */
    REG32(CCU_SPI_BGR) |= (1u << 17);              /* de-assert SPI1 reset */
    REG32(CCU_SPI1_CLK) = (1u << 31) | (0u << 24) | (0u << 8) | 2u;   /* HOSC/3 = 8 MHz */
    SPI(SPI_GCR) = (1u << 31);                     /* soft reset */
    while (SPI(SPI_GCR) & (1u << 31)) { }
    SPI(SPI_GCR) = (1u << 7) | (1u << 1) | 1u;     /* TP_EN, master, enable */
    /* mode 0, CS active low, software-owned CS held high, normal sample mode (<= 40 MHz) */
    SPI(SPI_TCR) = (1u << 13) | (1u << 7) | (1u << 6) | (1u << 2);
    SPI(SPI_FCR) = (1u << 31) | (1u << 15);        /* reset both FIFOs */
}
static void spi1_select(void *ctx, int asserted) {
    (void)ctx;
    uint32_t t = SPI(SPI_TCR);
    SPI(SPI_TCR) = asserted ? (t & ~(1u << 7)) : (t | (1u << 7));
    if (!asserted) delay_us(1);                    /* >= 2 SCK cycles CS# high (DS 4.5.1) */
}
static int spi1_transfer(void *ctx, const uint8_t *tx, uint8_t *rx, size_t n) {
    (void)ctx;
    while (n) {
        uint32_t k = n > 64u ? 64u : (uint32_t)n, i;
        uint64_t t0;
        SPI(SPI_MBC) = k;
        SPI(SPI_MTC) = k;
        SPI(SPI_BCC) = k;                          /* all single mode (STC = k) */
        for (i = 0; i < k; i++) REG8(SPI1_BASE + SPI_TXD) = tx ? tx[i] : 0u;
        SPI(SPI_ISR) = 0xFFFFFFFFu;                /* clear status (W1C) */
        SPI(SPI_TCR) |= (1u << 31);                /* XCH */
        t0 = cycles();
        while (!(SPI(SPI_ISR) & (1u << 12))) {     /* TC */
            if (cycles() - t0 > ASSUMED_MAX_HZ) return -1;   /* >= 1 s */
        }
        for (i = 0; i < k; i++) {
            uint8_t b = REG8(SPI1_BASE + SPI_RXD);
            if (rx) rx[i] = b;
        }
        if (tx) tx += k;
        if (rx) rx += k;
        n -= k;
    }
    return 0;
}

/* ---- BT820 platform ---- */
static void bt_reset(void *ctx, int level) { (void)ctx; gpio_set(PORT_D, 16, level); }
static void bt_delay(void *ctx, uint32_t ms) { (void)ctx; while (ms--) delay_us(1000); }

static bt820_dev g_dev;
static bt820_gfx g_gfx;

int main(void) {
    arc1_spi_hal hal = {0, spi1_select, spi1_transfer, now_us};
    bt820_platform plat = {0, bt_reset, bt_delay};
    bt820_boot_cfg cfg;
    bt820_boot_report rep;
    bt820_timing tim;
    int rc;

    uart_init();
    puts_("\nARC-1 Compact R07 F133 bring-up image (BUILD-ONLY until run on hardware)\n");
    kv("VER_REG 0x03000024   = ", REG32(SYSCFG_VER));
    kv("  BOOT_SEL_PAD[12:11]= ", (REG32(SYSCFG_VER) >> 11) & 3u);
    kv("  FEL_SEL_PAD[8]     = ", (REG32(SYSCFG_VER) >> 8) & 1u);
    kv("SID 0x03006210       = ", REG32(SID_BOOTSEL));
    kv("RTC fast boot        = ", REG32(RTC_FASTBOOT));

    /* T35 held in reset: PE8 output low (board also pulls it low). PE9 = CDONE input. */
    gpio_set(PORT_E, 8, 0);
    gpio_func(PORT_E, 8, 1);
    gpio_func(PORT_E, 9, 0);

    /* BT820 RST_N on PD16 (output), INT_N on PD17 (input) */
    gpio_set(PORT_D, 16, 0);
    gpio_func(PORT_D, 16, 1);
    gpio_func(PORT_D, 17, 0);
    spi1_init();

    if (bt820_init(&g_dev, &hal, 64, 128u << 20) || bt820_gfx_init(&g_gfx, &g_dev, &plat, 100000)) {
        puts_("driver init failed\n");
        return 1;
    }
    bt820_boot_cfg_default(&cfg);
    rc = bt820_boot(&g_gfx, &cfg, &rep);
    kv("bt820_boot result    = ", (uint32_t)rc);
    kv("  bus_error          = ", (uint32_t)rep.bus_error);
    kv("  REG_BOOT_STATUS    = ", rep.boot_status);
    kv("  REG_CHIP_ID        = ", rep.chip_id);
    kv("  REG_ID             = ", rep.reg_id);
    kv("  REG_CPURESET       = ", rep.cpureset);
    kv("  polls              = ", rep.polls_used);
    puts_(bt820_gfx_error_string(rc));
    puts_("\n");
    if (rc != BT820_GFX_OK) return 2;

    bt820_timing_candidate_1024x600(&tim);
    rc = bt820_scanout_start(&g_gfx, &tim);
    kv("scanout_start        = ", (uint32_t)rc);
    rc = bt820_test_frame(&g_gfx, 0x00, 0x40, 0xC0);
    kv("test_frame           = ", (uint32_t)rc);
    {
        uint32_t frames = 0;
        (void)bt820_read32(&g_dev, BT820_REG_FRAMES, &frames);
        kv("REG_FRAMES           = ", frames);
    }
    puts_("done: a lit blue screen is required before any display claim\n");
    return 0;
}

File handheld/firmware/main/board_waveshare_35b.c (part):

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// ---- pins (board_pins.h has the full map) ----------------------------------------------------
enum {
    PIN_I2C_SDA = 8, PIN_I2C_SCL = 7,
    PIN_LCD_CS = 12, PIN_LCD_SCLK = 5, PIN_LCD_D0 = 1, PIN_LCD_D1 = 2, PIN_LCD_D2 = 3, PIN_LCD_D3 = 4,
    PIN_LCD_BL = 6,
};
#define LCD_SPI_HOST SPI2_HOST
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    if (!s_trans_done) return false;
    spi_bus_config_t bus = {
        .sclk_io_num = PIN_LCD_SCLK,
        .data0_io_num = PIN_LCD_D0,
        .data1_io_num = PIN_LCD_D1,
        .data2_io_num = PIN_LCD_D2,
        .data3_io_num = PIN_LCD_D3,
        .max_transfer_sz = BOARD_LCD_W * LCD_MAX_LINES * 2,
    };
    if (spi_bus_initialize(LCD_SPI_HOST, &bus, SPI_DMA_CH_AUTO) != ESP_OK) { ESP_LOGE(TAG, "SPI bus failed"); return false; }
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// (same I2S pins and slot format, MCLK = 256 x fs, no PA pin). Differences:
// playback only (no RX channel), 48 kHz mono for the STRUTHIO mixer, and an
// I2S that plays silence on underrun.
enum { PIN_I2S_MCLK = 44, PIN_I2S_BCLK = 13, PIN_I2S_LRCK = 15, PIN_I2S_DOUT = 16, PIN_I2S_DIN = 14 };
#define AUDIO_RATE 48000
static i2s_chan_handle_t s_i2s_tx;
static esp_codec_dev_handle_t s_speaker;
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    std.slot_cfg.big_endian = false;
    std.slot_cfg.bit_order_lsb = false;
    std.gpio_cfg.mclk = (gpio_num_t)PIN_I2S_MCLK;
    std.gpio_cfg.bclk = (gpio_num_t)PIN_I2S_BCLK;
    std.gpio_cfg.ws = (gpio_num_t)PIN_I2S_LRCK;
    std.gpio_cfg.dout = (gpio_num_t)PIN_I2S_DOUT;
    std.gpio_cfg.din = I2S_GPIO_UNUSED;
    if (i2s_channel_init_std_mode(s_i2s_tx, &std) != ESP_OK || i2s_channel_enable(s_i2s_tx) != ESP_OK) {
        ESP_LOGE(TAG, "audio: I2S init failed");
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
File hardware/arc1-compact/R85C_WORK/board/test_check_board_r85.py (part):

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        find_r(p, "SPI0_MOSI", "GND")["value"] = "10k"
        self.fails(p, "boot_straps_00")

    def test_fpga_directly_on_spi0(self):             # R07 topology: FPGA MISO straight onto PC5
        p = copy.deepcopy(BASE)
        rewire(p, "U18", "V2", "SPI0_MISO")
        self.fails(p, "spi0_fpga_isolated")
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
    def test_nor_reset_without_fel_button(self):
        p = copy.deepcopy(BASE)
        sw = [c for c in p["components"] if c["part"] == "SW_B3U" and c["pins"]["1"]["net"] == "NOR_RESET_N"][0]
        rewire(p, sw["ref"], "1", "UNUSED_X")
        self.fails(p, "nor_boot_device")

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    def test_initn_not_readable(self):
        p = copy.deepcopy(BASE)
        u = comp(p, "U15")
        num = [n for n, x in u["pins"].items() if x["name"] == "PD0"][0]
        rewire(p, "U15", num, "UNUSED_Y")
        self.fails(p, "ecp5_sysconfig")

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    def test_rgmii_series_r_missing(self):             # direct connection: no termination at the F133 driver
        p = copy.deepcopy(BASE)
        r = find_r(p, "ETH_TXD1_F", "ETH_TXD1")
        rewire(p, r["ref"], "1" if r["pins"]["1"]["net"] == "ETH_TXD1" else "2", "ETH_TXD1_F")
        self.fails(p, "rgmii_link")

    def test_rgmii_series_r_wrong_value(self):
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
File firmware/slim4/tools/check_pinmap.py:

#!/usr/bin/env python3
"""Check the firmware's GPIO assignments against the PCB R28 board (pins unchanged from R23; R28 adds the radio).

Every SLIM4_GPIO_* in components/slim4_bsp/include/slim4_pins.h is looked up in the ESP32-P4 QFN-104 pin table
(GPIO -> package pad, datasheet section 2.2 / chip revision v3) and the board net on that U1 pad is read from
tools/u1_pad_nets.json, which ships with the firmware (U1's pad -> net table, taken from the board export
hardware/slim4/LAYERS/01_PCB/SLIM4_R28_PCB_LAYER.json). The net must be the one the define is named for. The display,
I2S and active-low control code paths are checked to use the defines.

The hardware self-test's table (SLIM4_ST_PINS in components/slim4_bsp/slim4_selftest_logic.c) is checked the same way:
each GPIO on its pad, each net on that pad (the unused pads it drives must have no net), and, where the board export is
at hand (inside the repository, or --board), each pull resistor's value and rail and the PWR_WAKE capacitor.

    python3 tools/check_pinmap.py                      # the bundled table: works from the firmware folder alone
    python3 tools/check_pinmap.py --board EXPORT.json  # a board export instead (e.g. a newer PCB revision)
    python3 tools/check_pinmap.py --write-table EXPORT.json   # refresh tools/u1_pad_nets.json from an export

Inside the full repository the bundled table is also compared with the repository's board export.
"""
import json, re, sys
from pathlib import Path

root = Path(__file__).resolve().parents[1]
table = root / 'tools/u1_pad_nets.json'
repo_board = root.parents[1] / 'hardware/slim4/LAYERS/01_PCB/SLIM4_R28_PCB_LAYER.json'


def u1_pads(export):
    """U1 pad number -> net name from a board export (*_PCB_LAYER.json)."""
    return {p['num']: p['netName'] for p in json.loads(Path(export).read_text())['pads']
            if p['ref'] == 'U1' and p['num'].isdigit()}


args = sys.argv[1:]
if args[:1] == ['--write-table']:
    src = Path(args[1])
    table.write_text(json.dumps({'board': src.name, 'u1_pads': dict(sorted(u1_pads(src).items(), key=lambda kv: int(kv[0])))},
                                indent=1) + '\n')
    print(f'wrote {table.relative_to(root)} from {src.name}')
    sys.exit(0)
if args[:1] == ['--board']:
    board_src = Path(args[1]); pads_by_num = u1_pads(board_src)
else:
    t = json.loads(table.read_text()); board_src = Path(t['board']); pads_by_num = t['u1_pads']
    if repo_board.exists() and u1_pads(repo_board) != pads_by_num:
        print(f'FAIL: tools/u1_pad_nets.json ({t["board"]}) differs from {repo_board.name}; '
              f'refresh it with --write-table {repo_board}')
        sys.exit(1)

# ESP32-P4 QFN-104: GPIO -> package pad, for the GPIOs this board uses (pin 9 is VDD_LP, so GPIO9.. sit one pad up;
# GPIO0 is pad 104, beside CHIP_PU on 103).
P4_PAD = {0: 104, 1: 1, 2: 2, 3: 3, 4: 4, 5: 5, 6: 6, 7: 7, 8: 8, 9: 10, 10: 11, 11: 12, 13: 14, 16: 17, 17: 18,
          24: 52, 25: 53, 35: 66, 43: 84, 44: 86, 46: 88,
          # unused GPIOs the self-test drives, beside tested nets (pads 13-19 run GPIO12-18; 85 is a supply pad,
          # so GPIO43/44/45/46 are pads 84/86/87/88)
          12: 13, 14: 15, 15: 16, 18: 19, 45: 87,
          # the radio (PCB R28+): GPIO39/40 are pads 80/81 (pad 79 is EN_DCDC); GPIO50 is pad 93 (91 is VDD_HP_3)
          39: 80, 40: 81, 50: 93}
# define name -> board net, where they differ
NET = {'BOOT_BTN': 'BOOT_STRAP'}

pins = {m[1]: int(m[2]) for m in re.finditer(r'#define\s+SLIM4_GPIO_(\w+)\s+GPIO_NUM_(\d+)', (root / 'components/slim4_bsp/include/slim4_pins.h').read_text())}
pads = {int(k): v for k, v in pads_by_num.items()}

bad = []
# the radio (PCB R28+): on a board export without any RADIO_ net (R27 and older) its pads must be free instead
radio_board = any(v.startswith('RADIO_') for v in pads.values())
for name, gpio in sorted(pins.items(), key=lambda t: t[1]):
    want = NET.get(name, name)
    pad = P4_PAD.get(gpio)
    got = pads.get(pad, 'no pad') if pad else 'GPIO not in the pin table'
    if name.startswith('RADIO_') and not radio_board:
        want = ''
    print(f'  GPIO{gpio:<3} pad {pad!s:>4}  {name:16} board net {got or "(none: no radio on this board)"}')
    if got != want:
        bad.append(f'SLIM4_GPIO_{name} = GPIO{gpio}: board pad {pad} is {got!r}, expected {want!r}')
# the console pins must stay the USB-Serial-JTAG pair
for gpio, net in ((24, 'USB_JTAG_DM'), (25, 'USB_JTAG_DP')):
    if pads.get(P4_PAD[gpio]) != net:
        bad.append(f'GPIO{gpio} pad {P4_PAD[gpio]} is {pads.get(P4_PAD[gpio])!r}, expected {net}')
source = (root / 'components/slim4_bsp/slim4_board.c').read_text()
for token in ['SLIM4_GPIO_BTN_LEFT', 'SLIM4_GPIO_BTN_RIGHT', 'SLIM4_GPIO_DART_LEFT', 'SLIM4_GPIO_DART_RIGHT', 'GPIO_PULLUP_DISABLE',
              'I2S_STD_PHILIPS_SLOT_DEFAULT_CONFIG', 'SLIM4_GPIO_I2S_BCLK', 'SLIM4_GPIO_I2S_LRCLK', 'SLIM4_GPIO_I2S_DOUT',
              'SLIM4_GPIO_AUDIO_SD_CTRL', 'SLIM4_GPIO_BACKLIGHT_PWM', 'SLIM4_GPIO_LCD_RESET_GATE']:
    if token not in source:
        bad.append(f'slim4_board.c does not use {token}')

# the self-test's pin table
ST = re.compile(r'\{(\d+), (\d+), "(\w+)", SLIM4_PULL_(\w+), SLIM4_ROLE_(\w+), (NULL|"[^"]*"), "([^"]*)", (true|false), (true|false), (true|false)\}')
st = [m.groups() for m in ST.finditer((root / 'components/slim4_bsp/slim4_selftest_logic.c').read_text())]
if len(st) < 20:
    bad.append(f'SLIM4_ST_PINS: only {len(st)} entries parsed')
export = Path(args[1]) if args[:1] == ['--board'] else (repo_board if repo_board.exists() else None)
parts = {}
if export:
    ex = json.loads(export.read_text())
    values = {p['ref']: p['value'] for p in ex['parts']}
    for p in ex['pads']:
        parts.setdefault(p['ref'], {})[p['num']] = p['netName']
VALUE = {'10K': '1002', '100K': '1003'}
for gpio, pad, net, pull, role, pull_part, load, drive_ok, cap, rc in st:
    gpio, pad = int(gpio), int(pad)
    want = '' if role == 'UNUSED' else net
    got = pads.get(pad, 'no pad')
    if P4_PAD.get(gpio) != pad:
        bad.append(f'self-test {net}: GPIO{gpio} is pad {P4_PAD.get(gpio)}, table says pad {pad}')
    if got != want:
        bad.append(f'self-test {net}: U1 pad {pad} is {got!r}, expected {want!r}')
    if gpio in pins.values() and NET.get(next(k for k, v in pins.items() if v == gpio), next(k for k, v in pins.items() if v == gpio)) != net:
        bad.append(f'self-test {net}: GPIO{gpio} is named differently in slim4_pins.h')
    if export and pull != 'NONE':
        ref = pull_part.strip('"').split()[0]
        rail = '3V3_SYS' if pull.startswith('UP') else 'GND'
        ends = set(parts.get(ref, {}).values())
        if ends != {net, rail}:
            bad.append(f'self-test {net}: {ref} joins {sorted(ends)}, expected {net} and {rail}')
        if VALUE[pull.split('_')[1]] not in values.get(ref, ''):
            bad.append(f'self-test {net}: {ref} is {values.get(ref)!r}, expected {pull.split("_")[1].lower()}')
    if export and cap == 'true':
        caps = [r for r, nets in parts.items() if r.startswith('C') and net in nets.values() and '104' in values.get(r, '')
                and set(nets.values()) == {net, 'GND'}]
        if not caps:
            bad.append(f'self-test {net}: marked with a capacitor, but no 100 nF from it to GND on the board')
    if export and role != 'UNUSED':
        on_board = [r for r, nets in parts.items() if r.startswith('C') and net in nets.values()]
        if on_board and cap != 'true':
            bad.append(f'self-test {net}: {", ".join(on_board)} on the net, but the table has no capacitor')
print(f'  self-test table: {len(st)} pins' + (f', pull resistors and capacitors checked in {export.name}' if export else
                                              ', resistor values not checked (no board export at hand)'))
if bad:
    print('FAIL:\n  ' + '\n  '.join(bad))
    sys.exit(1)
print(f'PASS: {len(pins)} firmware GPIO assignments and {len(st)} self-test pins match the board nets on U1 '
      f'({board_src.name}); USB-Serial-JTAG pair intact')
